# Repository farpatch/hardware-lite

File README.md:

# Farpatch Lite

A lite version of Farpatch -- a wireless debugger based on Black Magic Probe.

## Differences from the full version

* Farpatch Lite is smaller, and can fit into smaller areas
* There are no level shifters or voltage regulators -- your target MUST run at 3.3V!
* There are no damping resistors, which might affect signal integrity with the target
* There is no separate UART connector -- UART is integrated onto the SWD connector
* There is only one LED on the PCB

Farpatch Lite can be designed as a two-layer PCB, but a four-layer PCB stackup is preferred for signal integrity purposes.

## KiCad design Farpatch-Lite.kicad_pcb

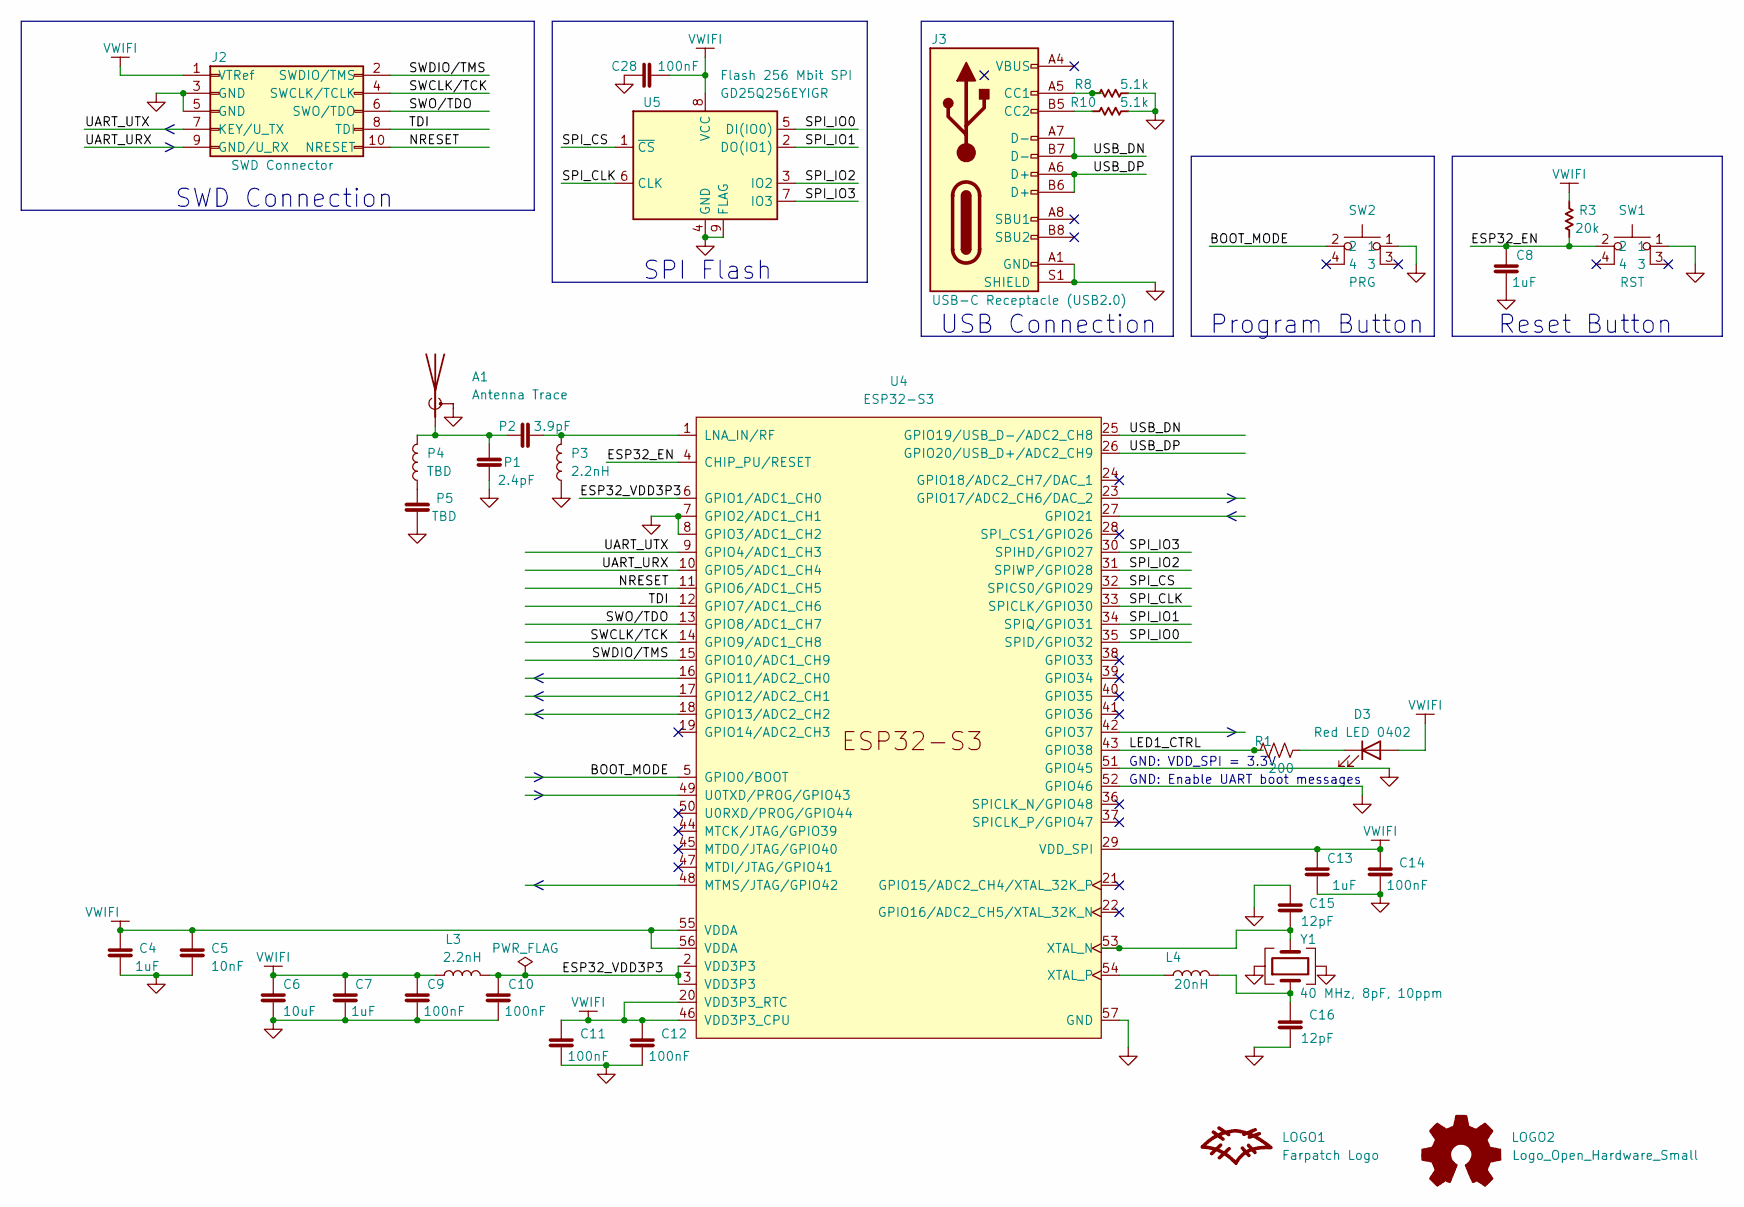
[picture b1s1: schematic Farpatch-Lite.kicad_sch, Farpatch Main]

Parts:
A1: Antenna Trace; Texas_SWRA117D_2.4GHz_Left
C4, C7, C8, C13: Cap 1uF 0402; C_0402_1005Metric; MFG PN ‎CL05A105MQ5NNNC‎
C5: Cap 10nF 0402; C_0402_1005Metric; MFG PN 885012205031
C6: Cap 10uF 0603; C_0603_1608Metric; MFG PN CL10A106KP8NNNC
C9, C10, C11, C12, C14, C28: Cap 100nF 0402; C_0402_1005Metric; MFG PN ‎CL05A104KA5NNNC‎
C15, C16: Cap 12pF 0402; C_0402_1005Metric; MFG PN ‎CC0402JRNPO9BN120‎
D3: Red LED 0402; LED_0402_1005Metric; MFG PN APHHS1005LSECK/J3-PF
J2: SWD Connector; PinHeader_2x05_P1.27mm_Vertical; MFG PN FTSH-105-01-F-DV-K
J3: USB-C Receptacle (USB2.0); USB_C_Receptacle_HRO_TYPE-C-31-M-12; MFG PN TYPE-C-31-M-12
L3: L 2.2nH 0402; L_0402_1005Metric; MFG PN LQW15AN2N2C10D
L4: L 20nH 0402; L_0402_1005Metric; MFG PN LQW15AN20NG00D
LOGO1: Farpatch Logo
LOGO2: Logo_Open_Hardware_Small; OSHW-Logo_5.7x6mm_SilkScreen
P1: Cap 2.4pF 0402; C_0402_1005Metric; MFG PN CC0402CRNPO9BN2R4
P2, P5: Cap 3.9pF 0402; C_0402_1005Metric; MFG PN CC0402CRNPO9BN3R9
P3, P4: L 2.7 nH 0402; L_0402_1005Metric; MFG PN L-07C2N7SV6T
R1: Res 200 0402; R_0402_1005Metric; MFG PN ‎RMCF0402JT200R‎
R3: Res 20k 0402; R_0402_1005Metric; MFG PN CR0402-FX-2002GLF
R8, R10: R 5.1k 0402; R_0402_1005Metric; MFG PN RMCF0402FT5K10
SW1, SW2: Pushbutton 4.2x3.2mm 250gf; SW_SPST_PTS810; MFG PN PTS810 SJK 250 SMTR LFS
U4: ESP32-S3; QFN-56-1EP_7x7mm_P0.4mm_EP5.6x5.6mm_ThermalVias; MFG PN ESP32-S3
U5: Flash 256 Mbit SPI; WSON-8_8x6mm_P1.27mm; MFG PN GD25Q256EYIGR
Y1: Crystal 40MHz 2016; Crystal_SMD_2016-4Pin_2.0x1.6mm; MFG PN XRCGB40M000F1S1BR0

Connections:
/BOOT_MODE: SW2.2, U4.5 (GPIO0/BOOT)
/ESP32_EN: C8.1, R3.1, SW1.2, U4.4 (CHIP_PU/RESET)
/ESP32_VDD3P3: C10.1, L3.2, U4.2 (VDD3P3), U4.3 (VDD3P3), U4.6 (GPIO1/ADC1_CH0)
/LED1_CTRL: R1.1, U4.43 (GPIO38)
/NRESET: J2.10 (NRESET), U4.11 (GPIO6/ADC1_CH5)
/SPI_CLK: U4.33 (SPICLK/GPIO30), U5.6 (CLK)
/SPI_CS: U4.32 (SPICS0/GPIO29), U5.1 (~CS)
/SPI_IO0: U4.35 (SPID/GPIO32), U5.5 (DI(IO0))
/SPI_IO1: U4.34 (SPIQ/GPIO31), U5.2 (DO(IO1))
/SPI_IO2: U4.31 (SPIWP/GPIO28), U5.3 (IO2)
/SPI_IO3: U4.30 (SPIHD/GPIO27), U5.7 (IO3)
/SWCLK/TCK: J2.4 (SWCLK/TCLK), U4.14 (GPIO9/ADC1_CH8)
/SWDIO/TMS: J2.2 (SWDIO/TMS), U4.15 (GPIO10/ADC1_CH9)
/SWO/TDO: J2.6 (SWO/TDO), U4.13 (GPIO8/ADC1_CH7)
/TDI: J2.8 (TDI), U4.12 (GPIO7/ADC1_CH6)
/UART_URX: J2.9 (GND/U_RX), U4.10 (GPIO5/ADC1_CH4)
/UART_UTX: J2.7 (KEY/U_TX), U4.9 (GPIO4/ADC1_CH3)
/USB_DN: J3.A7 (D-), J3.B7 (D-), U4.25 (GPIO19/USB_D-/ADC2_CH8)
/USB_DP: J3.A6 (D+), J3.B6 (D+), U4.26 (GPIO20/USB_D+/ADC2_CH9)
GND: A1.2 (Shield), C4.2, C5.2, C6.2, C7.2, C8.2, C9.2, C10.2, C11.2, C12.2, C13.2, C14.2, C15.1, C16.2, C28.1, J2.3 (GND), J2.5 (GND), J3.A1 (GND), J3.A12 (GND), J3.B1 (GND), J3.B12 (GND), J3.S1 (SHIELD), P1.1, P3.1, P5.1, R8.2, R10.2, SW1.1, SW2.1, U4.7 (GPIO2/ADC1_CH1), U4.8 (GPIO3/ADC1_CH2), U4.51 (GPIO45), U4.52 (GPIO46), U4.57 (GND), U5.4 (GND), U5.9 (FLAG), Y1.2, Y1.4
unnamed: A1.1 (A), P1.2, P2.1, P4.2
unnamed: C15.2, U4.53 (XTAL_N), Y1.3
unnamed: C16.1, L4.2, Y1.1
unnamed: D3.1 (K), R1.2
unnamed: J3.A5 (CC1), R8.1
unnamed: J3.A9 (VBUS), J3.B4 (VBUS)
unnamed: J3.B5 (CC2), R10.1
unnamed: L4.1, U4.54 (XTAL_P)
unnamed: P2.2, P3.2, U4.1 (LNA_IN/RF)
unnamed: P4.1, P5.2
VWIFI: C4.1, C5.1, C6.1, C7.1, C9.1, C11.1, C12.1, C13.1, C14.1, C28.2, D3.2 (A), J2.1 (VTRef), L3.1, R3.2, U4.20 (VDD3P3_RTC), U4.29 (VDD_SPI), U4.46 (VDD3P3_CPU), U4.55 (VDDA), U4.56 (VDDA), U5.8 (VCC)

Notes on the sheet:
Program Button
Reset Button
SWD Connection
GND: VDD_SPI = 3.3V
GND: Enable UART boot messages
SPI Flash
USB Connection

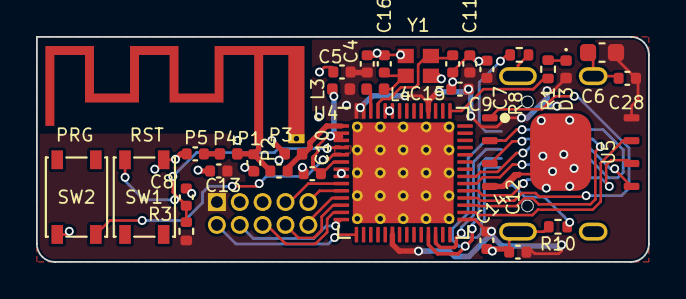
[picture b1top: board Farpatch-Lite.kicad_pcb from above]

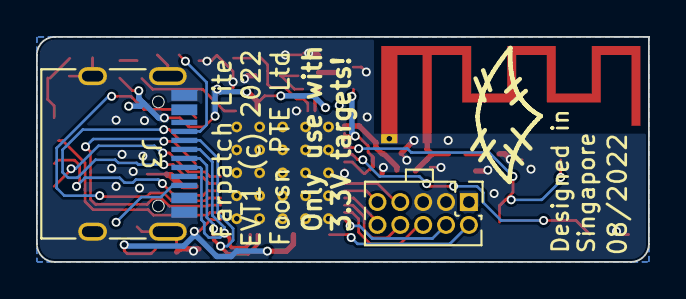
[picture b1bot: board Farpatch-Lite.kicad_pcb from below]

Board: 4 copper layers, 34.0 x 12.5 mm, 36 parts (3 on the bottom side), 31 nets.

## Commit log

2022-08-26 farpatch-lite: first draft
2022-08-26 farpatch-lite: Add fabrication data to PCB
2022-08-27 farpatch: finish layout and update README
2022-08-28 evt1: switch to 4-layer PCB
    While it's possible to route the board in two layers, four layers
    are more reliable.

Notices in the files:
Farpatch-Lite.kicad_pcb:
EVT1 (c) 2022
